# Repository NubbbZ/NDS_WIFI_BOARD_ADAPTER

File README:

# NDS WIFI Board Adapter

This simple adapter allows the user to connect their NDS Wifi board into a CH341A programer or similar, and easily access/flash the firmware chip.

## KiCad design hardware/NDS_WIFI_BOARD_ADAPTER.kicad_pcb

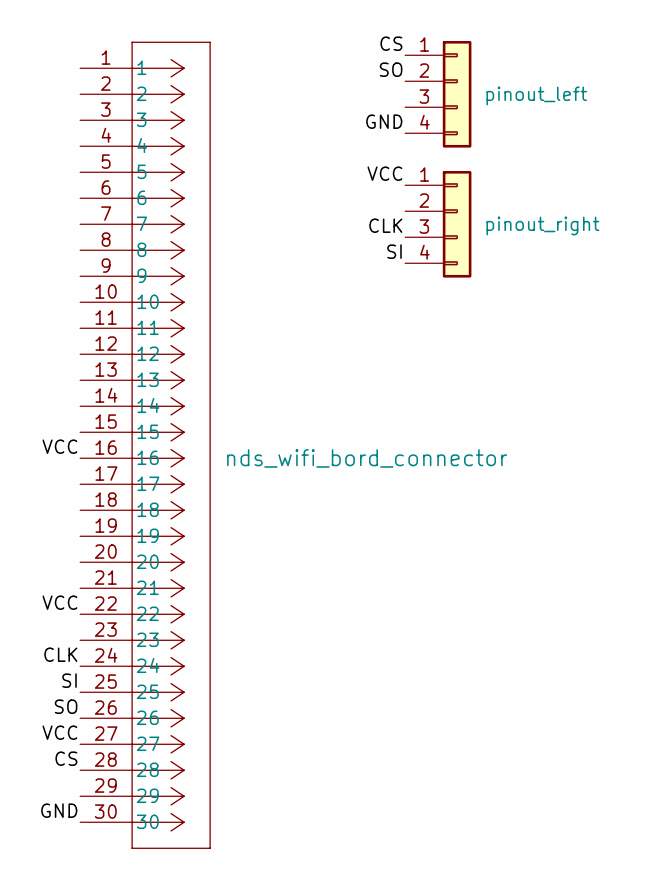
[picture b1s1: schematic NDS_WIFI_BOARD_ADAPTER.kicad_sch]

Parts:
J1: nds_wifi_bord_connector; CON_529910308
J2: pinout_left; PinHeader_1x04_P2.54mm_Vertical
J3: pinout_right; PinHeader_1x04_P2.54mm_Vertical

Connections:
/CLK: J1.24, J3.3
/CS: J1.28, J2.1
/GND: J1.30, J2.4
/SI: J1.25, J3.4
/SO: J1.26, J2.2
/VCC: J1.16, J1.22, J1.27, J3.1

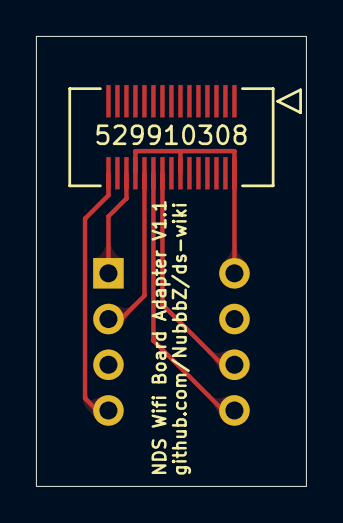
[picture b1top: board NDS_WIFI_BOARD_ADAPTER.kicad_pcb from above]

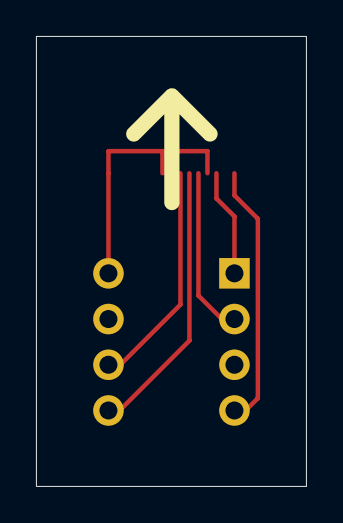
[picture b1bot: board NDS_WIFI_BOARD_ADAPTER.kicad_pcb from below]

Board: 2 copper layers, 15.0 x 25.0 mm, 3 parts (2 on the bottom side), 6 nets.
